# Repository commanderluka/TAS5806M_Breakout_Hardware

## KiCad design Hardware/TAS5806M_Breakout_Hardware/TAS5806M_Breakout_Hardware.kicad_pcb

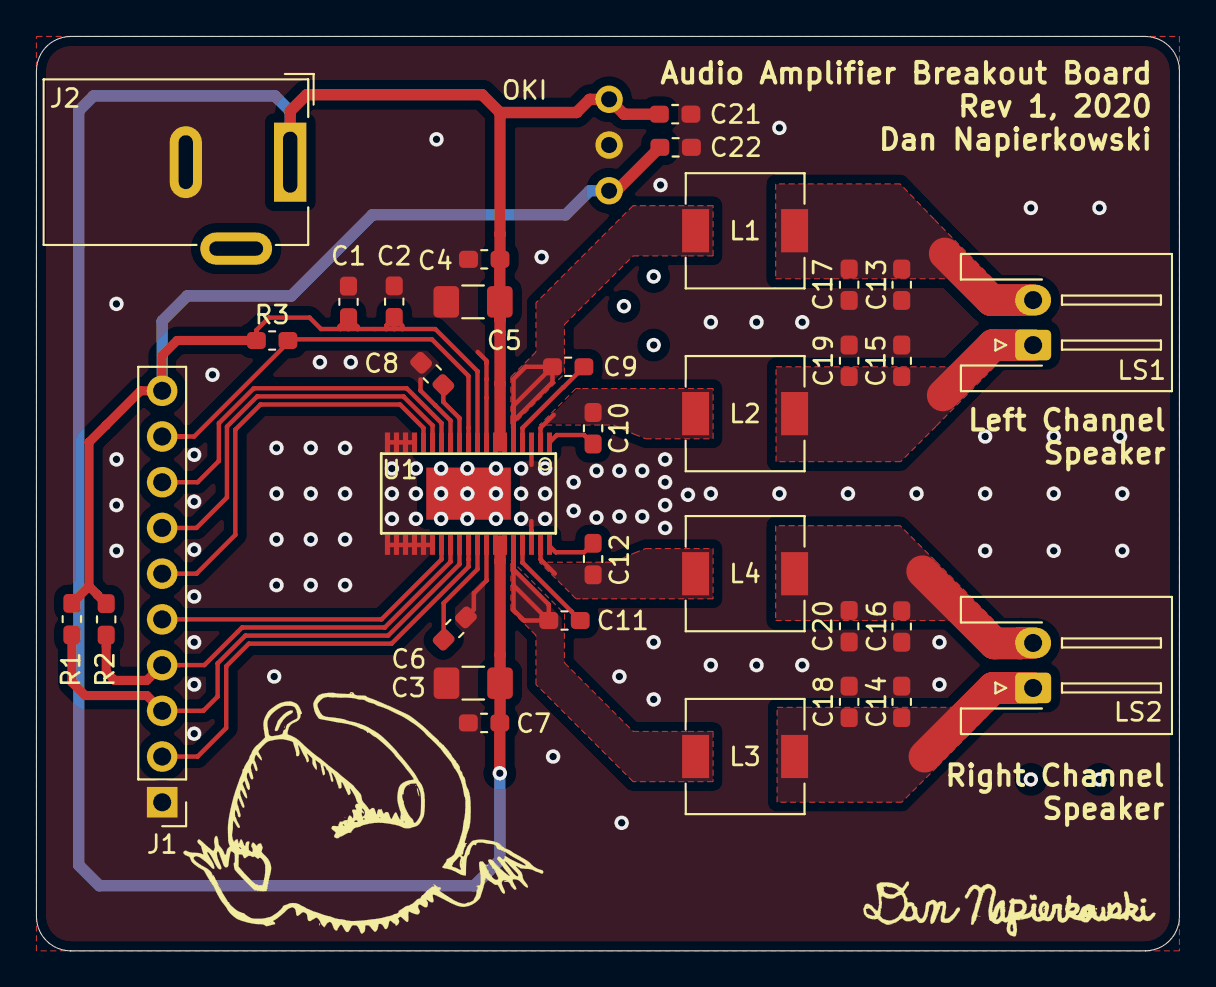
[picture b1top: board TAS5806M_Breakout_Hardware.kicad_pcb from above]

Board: 2 copper layers, 63.5 x 50.8 mm, 35 parts (0 on the bottom side), 25 nets.

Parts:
C1: 4.7uF; C_0603_1608Metric_Pad1.05x0.95mm_HandSolder
C2, C4, C7: 0.1uF; C_0603_1608Metric_Pad1.05x0.95mm_HandSolder
C3, C5: 22uF; C_1206_3216Metric_Pad1.42x1.75mm_HandSolder
C6, C8: 1uF; C_0603_1608Metric_Pad1.05x0.95mm_HandSolder
C9, C10, C11, C12: 0.22uF; C_0603_1608Metric_Pad1.05x0.95mm_HandSolder
C13, C14, C15, C16: 0.68uF; C_0603_1608Metric_Pad1.05x0.95mm_HandSolder
C17, C18, C19, C20: 1000pF; C_0603_1608Metric_Pad1.05x0.95mm_HandSolder
C21, C22: 10uF; C_0603_1608Metric_Pad1.05x0.95mm_HandSolder
J1: Headers; PinHeader_1x10_P2.54mm_Vertical
J2: Power Input; BarrelJack_Wuerth_6941xx301002
L1, L2, L3, L4: 4.7uH; L_6.3x6.3_H3
LS1, LS2: Speaker; JST_XH_S2B-XH-A-1_1x02_P2.50mm_Horizontal
R1, R2, R3: 4.7k; R_0603_1608Metric_Pad1.05x0.95mm_HandSolder
U1: TAS5806M
U2: OKI; OKI_Horizontal

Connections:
+3V3: C1.1, C2.1, C22.1, J1.10, R1.1, R2.1, R3.1, U1.9, U2.3
+12V: C3.1, C4.1, C5.1, C7.1, C21.1, J2.1, U1.6, U1.7, U1.32, U1.33, U2.1
ADR_Fault: J1.9, R3.2, U1.10
GND: C1.2, C2.2, C3.2, C4.2, C5.2, C6.2, C7.2, C8.2, C13.2, C14.2, C15.2, C16.2, C17.2, C18.2, C19.2, C20.2, C21.2, C22.2, J1.1, J2.2, U1.3, U1.8, U1.12, U1.16, U1.17, U1.18, U1.19, U1.20, U1.21, U1.22, U1.23, U1.24, U1.25, U1.31, U1.36, U1.39, U2.2
I2C_SCL: J1.3, R1.2, U1.28
I2C_SDA: J1.4, R2.2, U1.27
I2S_LRCLK: J1.8, U1.13
I2S_SCLK: J1.7, U1.14
I2S_SDIN: J1.6, U1.15
I2S_SDOUT: J1.5, U1.26
unnamed: C6.1, U1.30
unnamed: C8.1, U1.11
unnamed: C9.1, L1.1, U1.5
unnamed: C9.2, U1.4
unnamed: C10.1, L2.1, U1.2
unnamed: C10.2, U1.1
unnamed: C11.1, L3.1, U1.34
unnamed: C11.2, U1.35
unnamed: C12.1, L4.1, U1.37
unnamed: C12.2, U1.38
unnamed: C13.1, C17.1, L1.2, LS1.2
unnamed: C14.1, C18.1, L3.2, LS2.1
unnamed: C15.1, C19.1, L2.2, LS1.1
unnamed: C16.1, C20.1, L4.2, LS2.2
PDN: J1.2, U1.29

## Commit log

2020-10-30 Made PCB
2020-10-30 Finalized design, generated Gerbs
